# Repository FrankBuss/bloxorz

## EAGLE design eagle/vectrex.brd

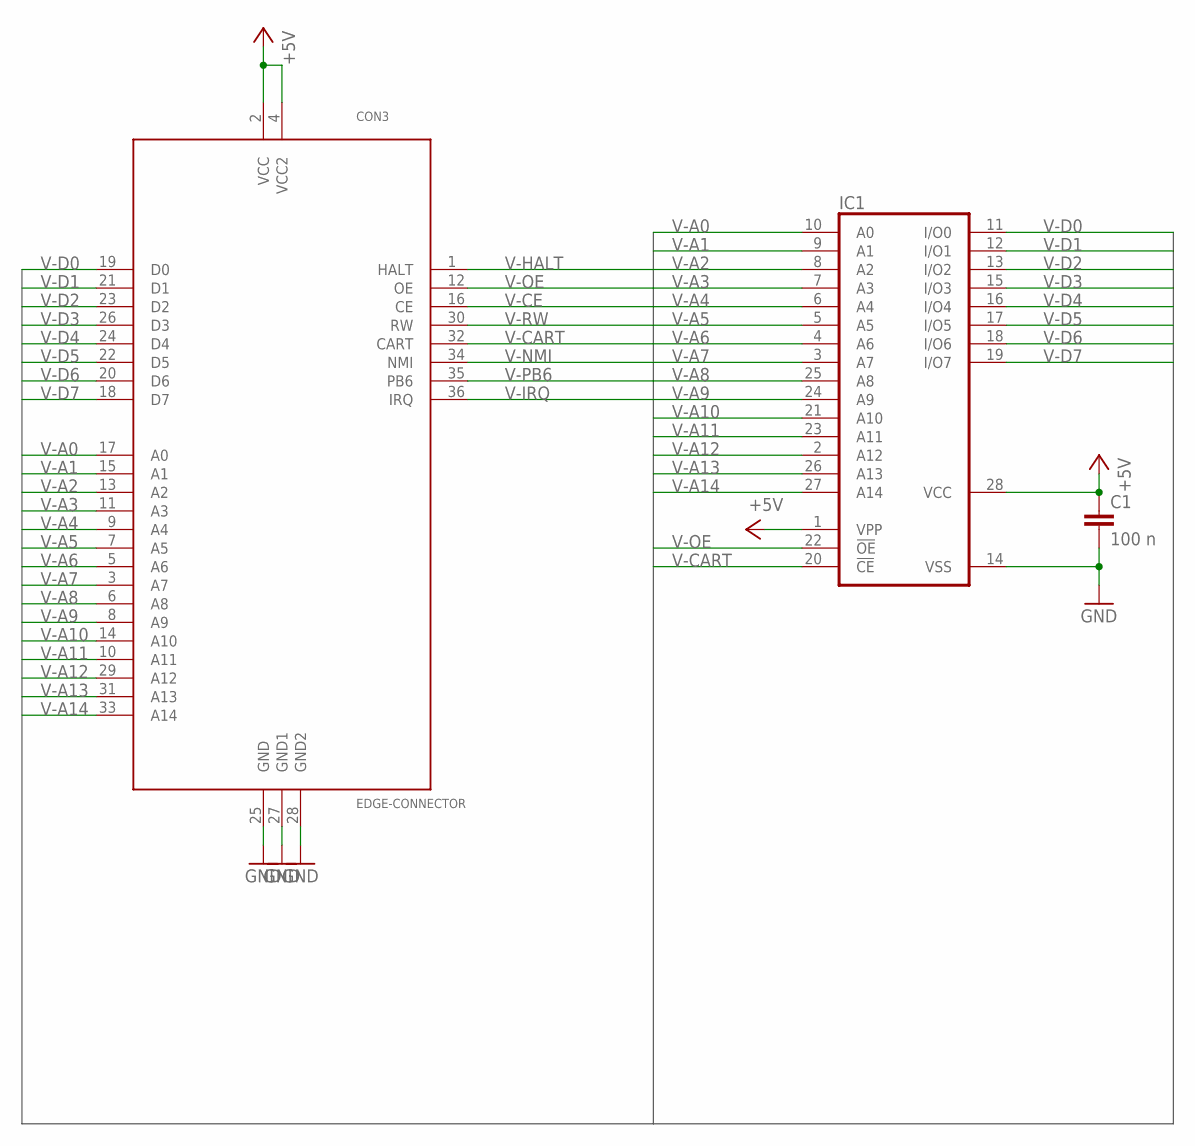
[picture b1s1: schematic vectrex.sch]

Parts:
C1: 100 n; C050-045X075
CON3: EDGE-CONNECTOR
IC1: 27C256AG; DIL28-6

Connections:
+5V: C1.1, CON3.2 (VCC), CON3.4 (VCC2), IC1.1 (VPP), IC1.28 (VCC)
GND: C1.2, CON3.25 (GND), CON3.27 (GND1), CON3.28 (GND2), IC1.14 (VSS)
V-A0: CON3.17 (A0), IC1.10 (A0)
V-A1: CON3.15 (A1), IC1.9 (A1)
V-A2: CON3.13 (A2), IC1.8 (A2)
V-A3: CON3.11 (A3), IC1.7 (A3)
V-A4: CON3.9 (A4), IC1.6 (A4)
V-A5: CON3.7 (A5), IC1.5 (A5)
V-A6: CON3.5 (A6), IC1.4 (A6)
V-A7: CON3.3 (A7), IC1.3 (A7)
V-A8: CON3.6 (A8), IC1.25 (A8)
V-A9: CON3.8 (A9), IC1.24 (A9)
V-A10: CON3.14 (A10), IC1.21 (A10)
V-A11: CON3.10 (A11), IC1.23 (A11)
V-A12: CON3.29 (A12), IC1.2 (A12)
V-A13: CON3.31 (A13), IC1.26 (A13)
V-A14: CON3.33 (A14), IC1.27 (A14)
V-CART: CON3.32 (CART), IC1.20 (!CE)
V-CE: CON3.16 (CE)
V-D0: CON3.19 (D0), IC1.11 (I/O0)
V-D1: CON3.21 (D1), IC1.12 (I/O1)
V-D2: CON3.23 (D2), IC1.13 (I/O2)
V-D3: CON3.26 (D3), IC1.15 (I/O3)
V-D4: CON3.24 (D4), IC1.16 (I/O4)
V-D5: CON3.22 (D5), IC1.17 (I/O5)
V-D6: CON3.20 (D6), IC1.18 (I/O6)
V-D7: CON3.18 (D7), IC1.19 (I/O7)
V-HALT: CON3.1 (HALT)
V-IRQ: CON3.36 (IRQ)
V-NMI: CON3.34 (NMI)
V-OE: CON3.12 (OE), IC1.22 (!OE)
V-PB6: CON3.35 (PB6)
V-RW: CON3.30 (RW)

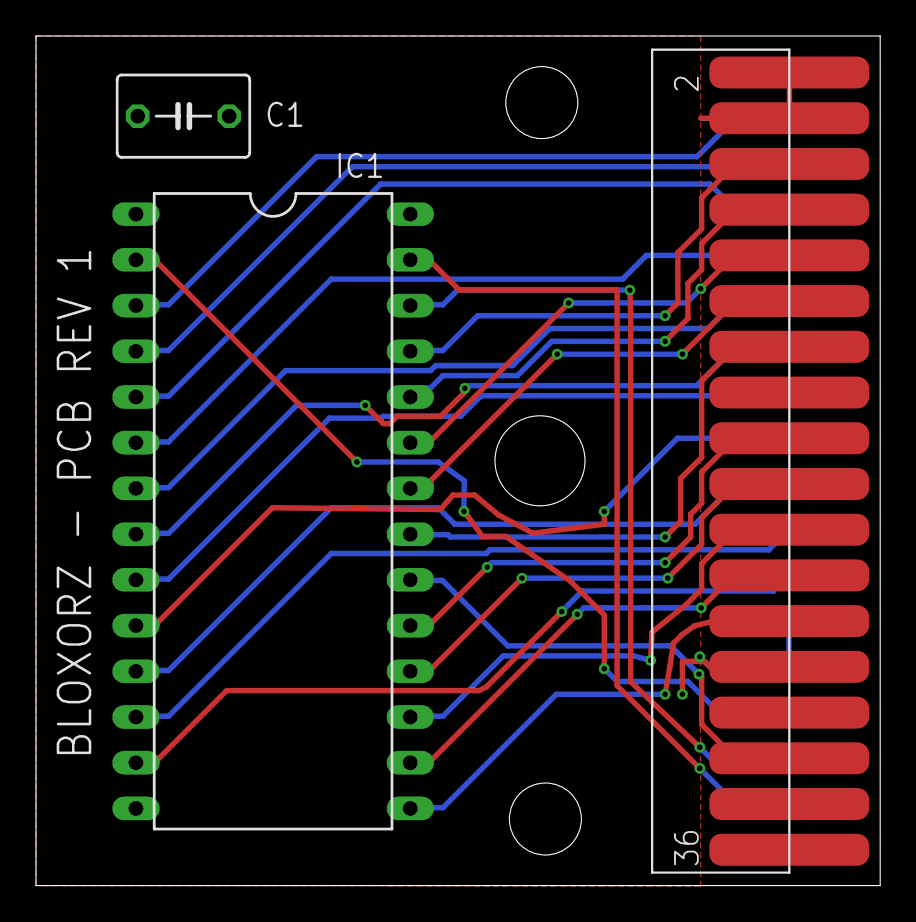
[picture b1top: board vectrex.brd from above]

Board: 2 copper layers, 46.9 x 47.2 mm, 3 parts (0 on the bottom side), 27 nets.

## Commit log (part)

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2017-12-16 initial version
2017-12-16 initial version of the game
2017-12-17 original level from the Flash game
2017-12-27 PCB rev 3
2018-01-07 rev 4
2018-01-14 highscore save/load on PIC implemented
2018-01-14 new revision D of the PIC datasheet
2018-01-25 new bank switching and new field draw function by Malban
2018-01-26 new command to enable programmer mode, so that HALT can be low in normal use
2018-09-02 music added
2018-09-10 initial MonoGame version for Windows
2018-10-02 shift register bugfix, thanks to Malban
2018-10-06 VIA bugfix for better font display
2018-10-09 first 23 levels
2019-02-18 split mode implemented
2019-02-18 48 k ROM support
2019-07-27 splitted levels in 2 banks
2019-07-28 bankswitching for Monogame emulator implemented
2019-09-30 new arcade mode
2020-10-15 current version
2020-10-16 solver changes to breadth first and more object oriented
2020-10-16 fixed bug that switches can't be activated in split mode and keyboard input for playing with cursor keys
2020-10-16 memoization optiomization and enabling all levels
2020-10-16 one solution for all levels added
2020-10-17 all levels are solved with improved code from Johan Wind
2020-10-17 split mode bugfixing and cleanups
2020-10-17 indention fixed
2020-10-17 split mode and other minor bugfixes
2021-06-26 porting the Godot project to Unity
2021-10-14 new version from Malban
2023-03-20 fixed bank switching problem
2023-03-26 cleanup of PIC command emulation and implemented highscore save function in Unity emulator
2023-04-02 formatted C code
2024-01-27 removed generated files
2024-01-27 new gitignore for generated Vide files
2024-01-27 started arcade mode
2024-01-27 avoid deleting the emptyfile in ignored github directory
2024-01-27 game over screen in arcade mode
2024-02-04 empty files to keep the directory
2024-02-04 fixed emptyfile handling
2024-02-04 more for arcade mode
